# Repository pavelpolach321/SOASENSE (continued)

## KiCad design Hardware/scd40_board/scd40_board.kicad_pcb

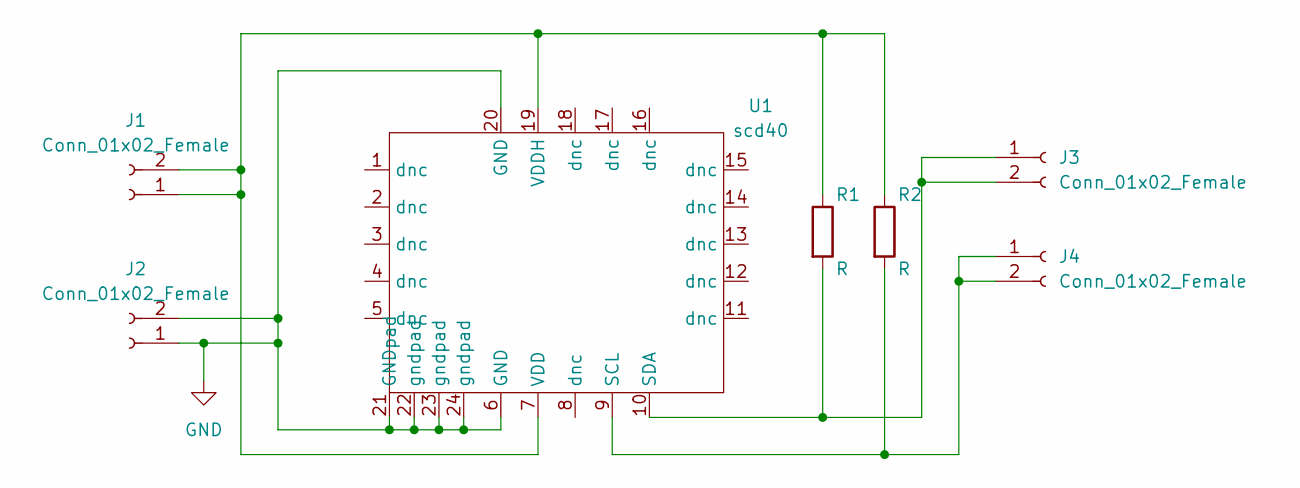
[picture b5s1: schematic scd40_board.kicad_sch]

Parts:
J1, J2, J3, J4: Conn_01x02_Female; PinHeader_1x02_P2.54mm_Vertical
R1, R2: R; R_0805_2012Metric
U1: scd40; SCD40

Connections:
GND: J2.1, J2.2, U1.6 (GND), U1.20 (GND), U1.21 (GNDpad), U1.22 (gndpad), U1.23 (gndpad), U1.24 (gndpad)
unnamed: J1.1, J1.2, R1.1, R2.1, U1.7 (VDD), U1.19 (VDDH)
unnamed: J3.1, J3.2, R1.2, U1.10 (SDA)
unnamed: J4.1, J4.2, R2.2, U1.9 (SCL)

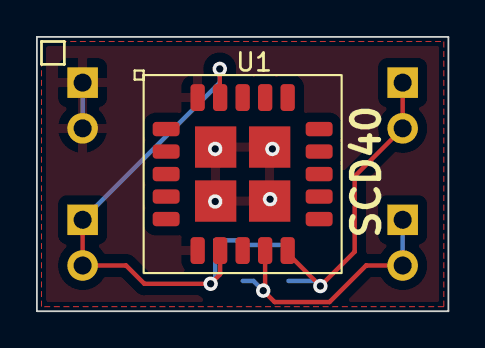
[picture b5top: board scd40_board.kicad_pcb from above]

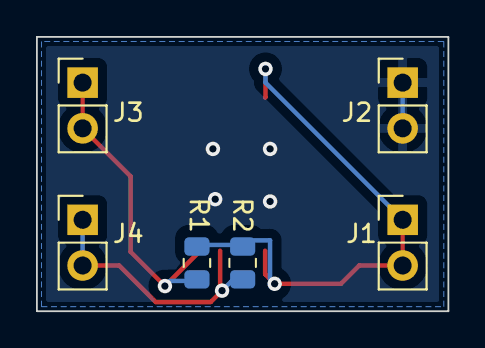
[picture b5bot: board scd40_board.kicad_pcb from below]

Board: 2 copper layers, 22.9 x 15.2 mm, 7 parts (6 on the bottom side), 4 nets.

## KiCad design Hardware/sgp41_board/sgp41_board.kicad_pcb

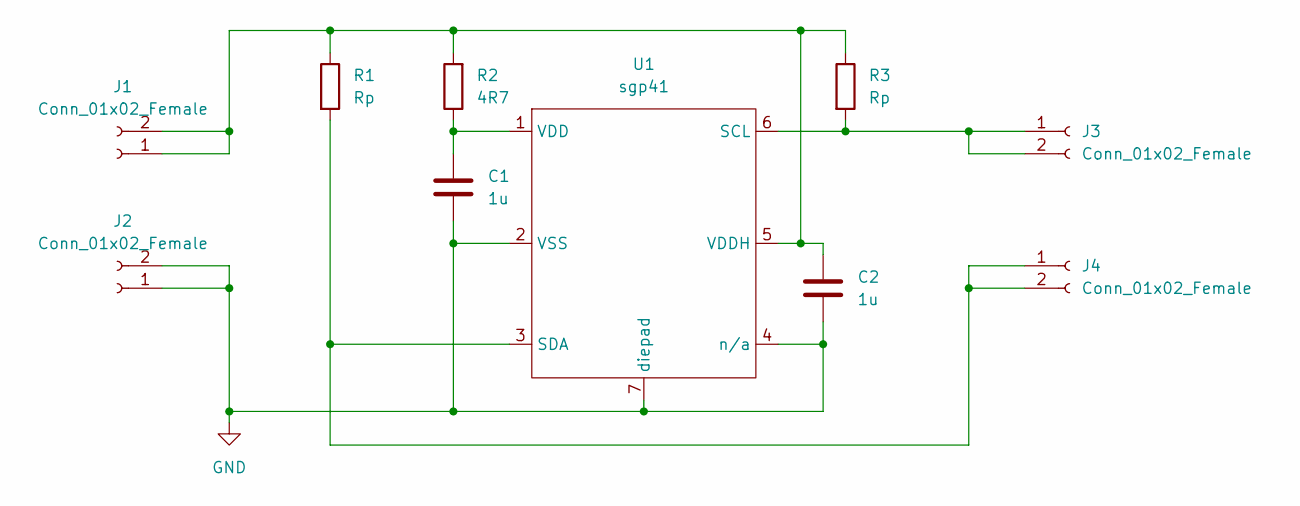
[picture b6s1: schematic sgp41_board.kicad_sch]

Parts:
C1, C2: 1u; C_0805_2012Metric
J1, J2, J3, J4: Conn_01x02_Female; PinHeader_1x02_P2.54mm_Vertical
R1, R3: Rp; R_0805_2012Metric
R2: 4R7; R_0805_2012Metric
U1: sgp41

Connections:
GND: C1.1, C2.2, J2.1, J2.2, U1.2 (VSS), U1.4 (n/a), U1.7 (diepad)
unnamed: C1.2, R2.1, U1.1 (VDD)
unnamed: C2.1, J1.1, J1.2, R1.1, R2.2, R3.1, U1.5 (VDDH)
unnamed: J4.1, J4.2, R1.2, U1.3 (SDA)
unnamed: J3.1, J3.2, R3.2, U1.6 (SCL)

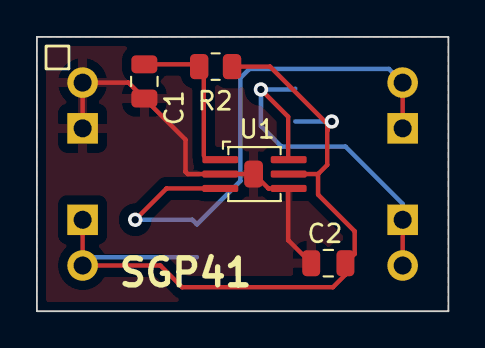
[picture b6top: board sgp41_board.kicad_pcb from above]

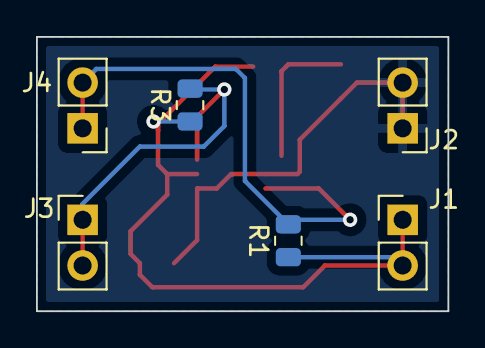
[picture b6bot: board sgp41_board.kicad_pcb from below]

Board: 2 copper layers, 22.9 x 15.2 mm, 10 parts (6 on the bottom side), 5 nets.

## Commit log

2023-02-01 Lets run the board without sensors
2023-02-01 Add LIGHT-02 node credentials
2023-02-07 Watchdog enabled
2023-02-07 v0.47
2023-11-18 Ver02dev01-06
2023-11-19 qad scd4x add
2024-01-11 It is as it is
